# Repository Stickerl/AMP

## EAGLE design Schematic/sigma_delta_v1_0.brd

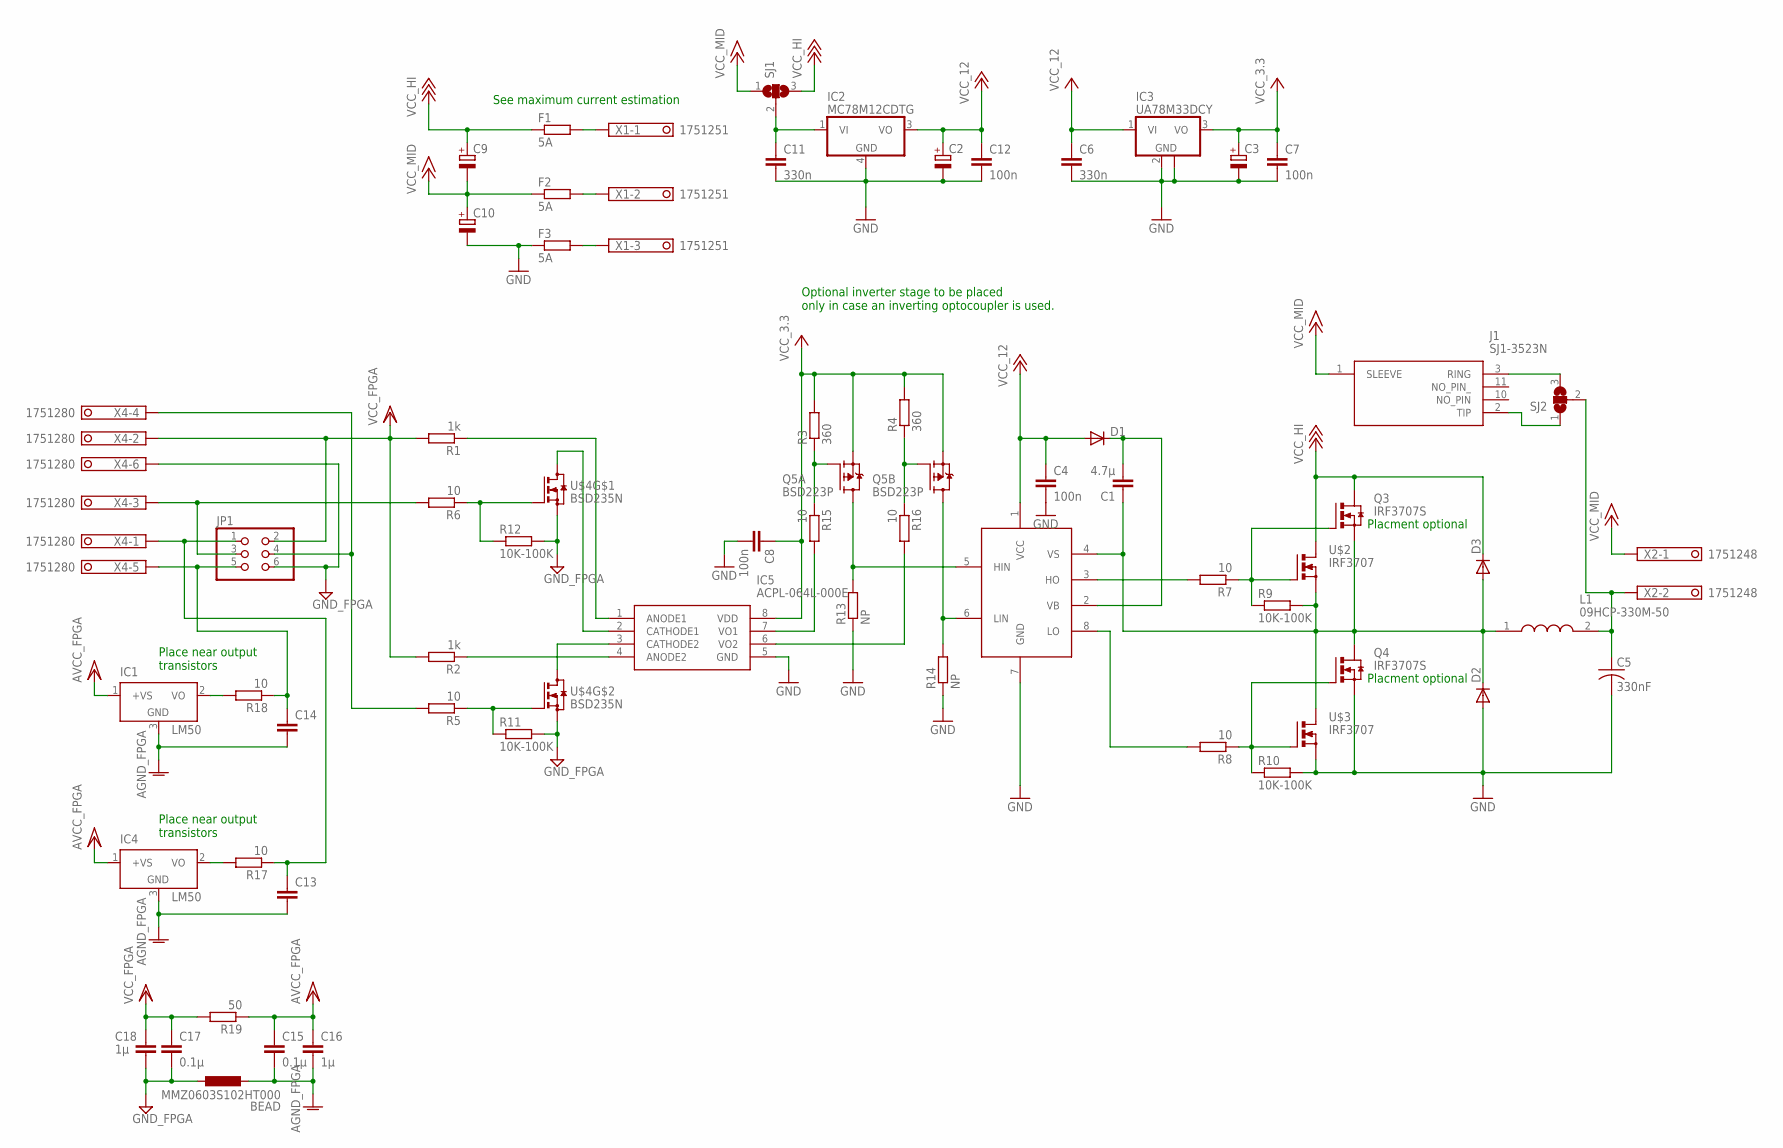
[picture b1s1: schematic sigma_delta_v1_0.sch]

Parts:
BEAD: MMZ0603S102HT000; L2012C
C1: 4.7µ; C0805K
C2, C3: CPOL-EUUD-6,3X7,7; UD-6,3X7,7_NICHICON
C4: 100n; C0805
C5: 330nF; C2220K
C6, C11: 330n; C0603
C7, C8, C12: 100n; C0603
C9, C10: CPOL-EUUD-10X10; UD-10X10_NICHICON
C13, C14: C-EUC0603; C0603
C15, C17: 0.1µ; C0603
C16, C18: 1µ; C0603
D1, D2, D3: DIODE-DO214AC; DO214AC
F1, F2, F3: 5A; M1206
IC1, IC4: LM50; SOT23
IC2: MC78M12CDTG; DPACK_3
IC3: UA78M33DCY; SOT223
IC5: ACPL-064L-000E; SOIC127P599X330-8N
J1: SJ1-3523N; SJ13523N
JP1: PINHD-2X3_2.54; 2X03
L1: 09HCP-330M-50; 09HCP330M50
Q3, Q4: IRF3707S; D2PACK
Q5: BSD223P; SOT363_INFINEON
R1, R2: 1k; R0603
R3, R4: 360; R0603
R5, R6, R7, R8, R15, R16, R17, R18: 10; R0603
R9, R10, R11, R12: 10K-100K; R0603
R13, R14: NP; R0603
R19: 50; R0603
SJ1: SJ2W; SJ_2
SJ2: SJ2WW; SJ_2W
U$1: IR2011; SO08
U$2, U$3: IRF3707; TO220BV
U$4: BSD235N; SOT65P210X100-6N
X1: 1751251
X2: 1751248
X4: 1751280

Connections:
AGND_FPGA: BEAD.2, C13.2, C14.2, C15.2, C16.2, IC1.3 (GND), IC4.3 (GND)
AVCC_FPGA: C15.1, C16.1, IC1.1 (+VS), IC4.1 (+VS), R19.1
GND: C2.-, C3.-, C4.2, C5.2, C6.2, C7.2, C8.2, C10.-, C11.2, C12.2, D2.A, F3.1, IC2.4 (GND), IC3.2 (GND), IC3.4 (GND), IC5.5 (GND), Q4.3 (S), R10.2, R13.1, R14.1, U$1.7 (GND), U$3.S
GND_FPGA: BEAD.1, C17.2, C18.2, JP1.6, R11.2, R12.2, U$4.1 (S), U$4.4 (S), X4.6
H_BRIDGE_MID: C1.1, D2.C, D3.A, L1.1, Q3.3 (S), Q4.2 (D), R9.2, U$1.4 (VS), U$2.S, U$3.D
unnamed: JP1.3, R6.2, X4.3
unnamed: JP1.4, R5.2, X4.4
unnamed: IC5.2 (CATHODE1), U$4.6 (D)
unnamed: IC5.3 (CATHODE2), U$4.3 (D)
unnamed: IC5.1 (ANODE1), R1.1
unnamed: IC5.4 (ANODE2), R2.1
unnamed: Q5.2 (G), R3.1, R15.1
unnamed: IC5.6 (VO2), R16.2
unnamed: F3.2, X1.3
unnamed: C5.1, L1.2, SJ2.2, X2.2
unnamed: R5.1, R11.1, U$4.5 (G)
unnamed: R6.1, R12.1, U$4.2 (G)
unnamed: R7.2, U$1.3 (HO)
unnamed: Q3.1 (G), R7.1, R9.1, U$2.G
unnamed: Q4.1 (G), R8.1, R10.1, U$3.G
unnamed: R8.2, U$1.8 (LO)
unnamed: C1.2, D1.C, U$1.2 (VB)
unnamed: F1.2, X1.1
unnamed: Q5.6 (D), R13.2, U$1.5 (HIN)
unnamed: F2.2, X1.2
unnamed: Q5.3 (D), R14.2, U$1.6 (LIN)
unnamed: Q5.5 (G), R4.1, R16.1
unnamed: IC4.2 (VO), R17.2
unnamed: J1.3 (RING), SJ2.3
unnamed: J1.2 (TIP), SJ2.1
unnamed: IC5.7 (VO1), R15.2
unnamed: C11.1, IC2.1 (VI), SJ1.2
unnamed: C13.1, JP1.1, R17.1, X4.1
unnamed: C14.1, JP1.5, R18.1, X4.5
unnamed: IC1.2 (VO), R18.2
VCC_3.3: C3.+, C7.1, C8.1, IC3.3 (VO), IC5.8 (VDD), Q5.1 (S), Q5.4 (S), R3.2, R4.2
VCC_12: C2.+, C4.1, C6.1, C12.1, D1.A, IC2.3 (VO), IC3.1 (VI), U$1.1 (VCC)
VCC_FPGA: C17.1, C18.1, JP1.2, R1.2, R2.2, R19.2, X4.2
VCC_HI: C9.+, D3.C, F1.1, Q3.2 (D), SJ1.3, U$2.D
VCC_MID: C9.-, C10.+, F2.1, J1.1 (SLEEVE), SJ1.1, X2.1

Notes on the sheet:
Placment optional
Place near output transistors
See maximum current estimation
Optional inverter stage to be placed only in case an inverting optocoupler is used.

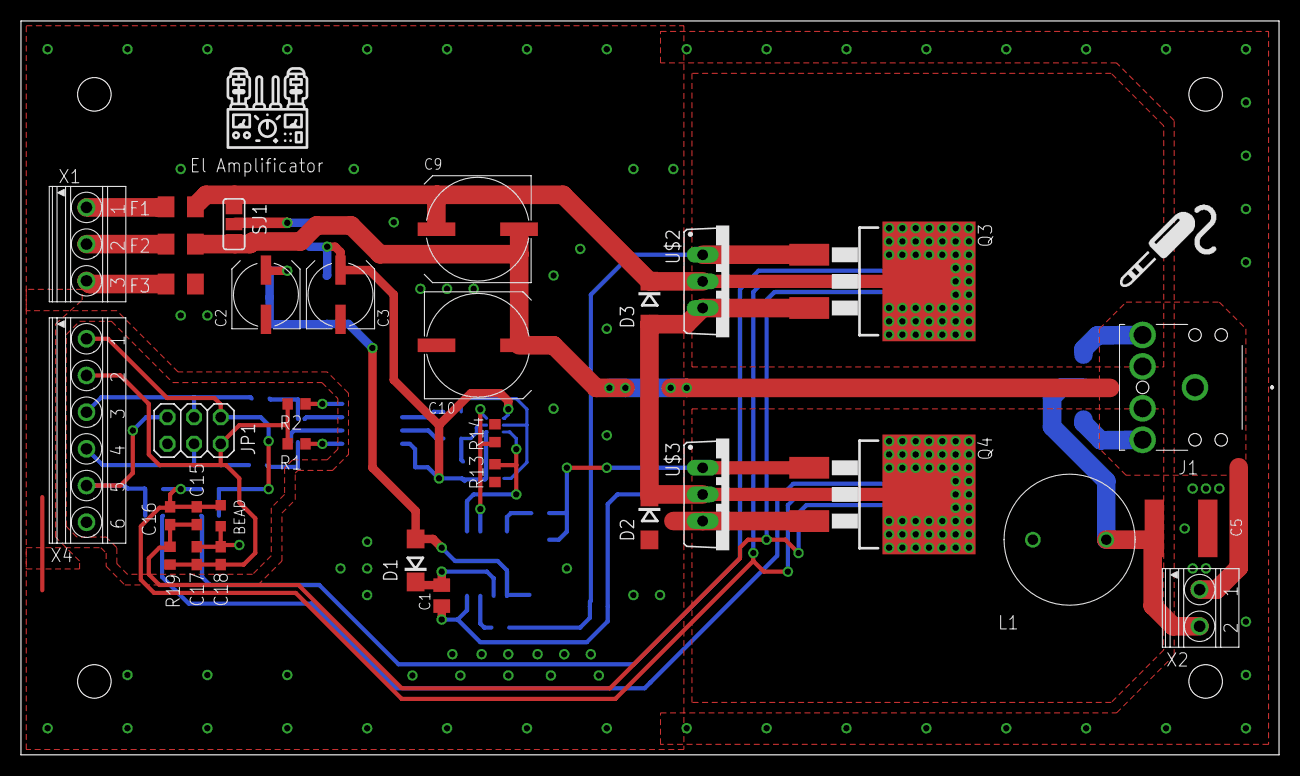
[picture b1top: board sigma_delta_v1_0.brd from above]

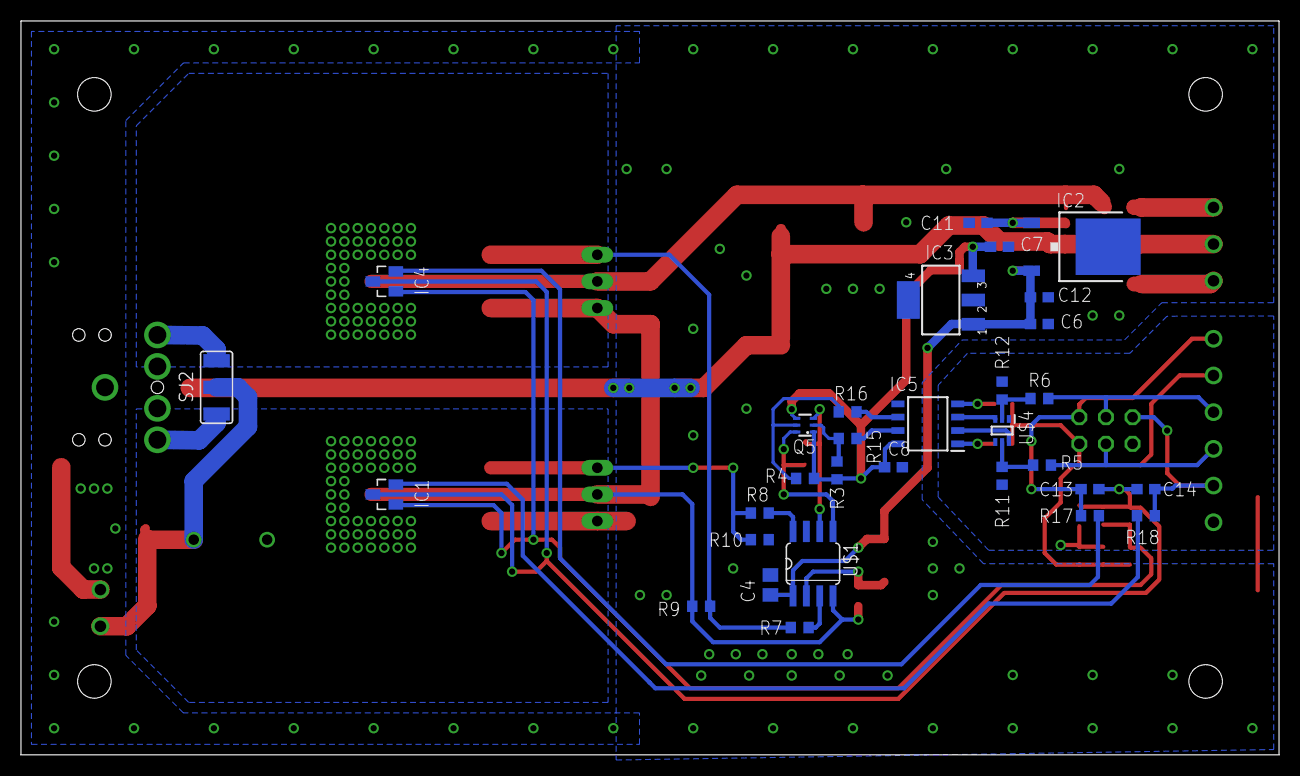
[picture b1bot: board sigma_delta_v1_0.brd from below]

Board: 2 copper layers, 120.0 x 70.0 mm, 64 parts (31 on the bottom side), 40 nets.

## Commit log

2020-01-31 copy contents from svn repo
2020-01-31 added script for sending audio data to the amp
2020-01-31 copied not committed svn files
2020-01-31 several bugfixes (project is not able to be compile)
2020-01-31 added files for AudioStreamFifo
2020-01-31 fixed a typo
2020-02-07 Added LabView project for simulation of the sigma delta structure.
2020-02-07 Added LabView project for debug bus and some additional vi's
2020-02-07 Moved Amplitude_compare.vi and Csv_read.vi into the debug bus project
2020-02-07 bug fixes in design, rework of UART_Tx_driver.vhd
2020-02-07 Added documents of DE0-Nano board.
2020-02-14 added pin assignment for UART pins commented all debugging outputs of sigmar delta modulator itself Received UART bytes are send out on debugging bus channel 0
2020-02-28 debugged tx driver (remainding buffer size seems to be transmitted correctly)
2020-03-13 replaced tabs with spaces
2020-03-13 bugfix: AudioFifo was in permanent reset reworked process for sending out debug data of audio stream before and after the FIFO upgraded AudioFifo version to version 18.1
2020-03-13 added experimental sending of several bytes in the HDLC protocol
2020-03-13 "made myRio application as startup application and changed View-Parallel-Port-Data.vi for debugging"
2020-03-13 added missing files of previous commit
2020-03-22 created a gitignore file
2020-03-22 added pins assignment of AMP project
2020-03-22 update git ignore file
2020-03-22 inverted bytes array sent to DUT
2020-03-22 added reset path to hdlc decoder
2020-03-22 added reading of CSV file to compare sent data with debug data
2020-03-22 added .csv generation to view-parallel-port-data vi and tested reading the file with python
2020-03-27 created a sub vi for csv file generation containing measuerment data
2020-03-27 forgot to save and close Labview before previous commit
2020-03-27 Implemented comparing a data stream sent to the FPGA and received back via csv-file
2020-03-27 Read in csv file and compare the data against an expectation -> verify communication stability
2020-03-28 set up testbench for validating transceived data via UART and debug bus
2020-04-03 reworked hdlc decoder. Bugfix: waiting for first frame delimiter. Endianess issue fixed (tested)
2020-04-10 removed LED and debug bus connection to the HDLC decoder output
2020-04-10 removed adc entity form top entity
2020-04-10 implemented sinus streaming in python. Somehow the buffersize response is worng
2020-04-17 added confirmation that this project is awesome!
2020-04-17 intermediate version of debugging uart data streaming.
2020-04-24 fixed first buffer fill level response and changed uart baudrate to 2mbit
2020-04-24 added debug bus connection to the HDLC decoder output again Revert "removed LED and debug bus connection to the HDLC decoder output"
    This reverts commit ebde65a294942e63edc34fb96ba66c52af91d544.
2020-04-24 commented out audiosample output on debugging bus
2020-04-30 fixed hdlc decoding issue. Audiostreaming currently works with a sine amplitude of 1000 only. Underflow exception occures within the python script
2020-05-08 fixed bugs in Uart transmission and successfully verified bitstream (filtered) vs simulation output
2020-05-08 added eagle schematic
2020-05-22 unsuccessfully tried to stream a audio file
2020-07-10 first successfull stream of an audio file to the FPGA
2020-07-10 added connection between VS and the Load within the scematic
2020-08-07 started reworking the scematic
2020-08-30 Added documents and eagle librarys as well as Part_List.xlsx
2020-08-30 Add data sheet for audio jack
2020-08-30 added datasheetd and pinheader library
2020-08-30 intermediate commit before rework of the input stage
2020-08-30 Added datasheet for dual channel N MOS BSD223P. Added several parts to the Part_list
2020-08-30 Added NMOS pair for data transfer
2020-09-25 adde datasheet of BSD235N
2020-09-25 continued replaceing parts with smd components
2020-10-02 Add data sheet for optocoupler.
2020-10-02 Add optocoupler to part list
2020-10-02 finished rework of the Schematic and cleaned up repository
2020-10-02 started layout design
2020-10-09 continued layouting and added analog decoupling for temperature sensors
2020-10-16 continued routing and added ferrit bead datasheet
2020-10-23 added FPGA_GND polygon to the top layer
2020-10-23 intermediate commit prior changing the net to mm
2020-10-23 Finished layouting. DRC pending
2020-11-01 adapted wireing width of power stage and exchanged bootstrap capacitor
2020-11-06 ERC and DRC done. Ready for production.
2020-11-06 added mounting drills
2020-11-06 generated gerber files for manufacturing
2020-11-13 add mouser link to fuse
2020-11-13 add 3.3V regulator to part list
2020-11-13 added parts to part list
2020-11-13 dummy change to check connectivity to repository
2020-11-13 revert last change
2020-11-22 Removed datasheet of deprecated optocouppler
2020-11-22 added non inverting optocoupler as suppliment of ACPL-064L
2020-11-22 added comment to the scematic regarding the inverter stage
2020-11-27 Add Maxima trial file
2020-12-04 started transferring math work from maple to maxima
2020-12-18 reworked gerber files
2021-01-01 add block diagram of first order sigma delta
2021-01-01 added transfer functions for E and X
2021-01-01 corrected an error in noise transfer function
2021-01-02 added maple files and added calculations fo first order sigma delta modulator
2021-01-08 debugged of 3d plot of transfer function
2021-01-08 Banana commit to verify, that i can still access the repository while the git config was changed
2021-10-29 It is now possible to generate a 3d plot of the abs() of He(z)
2021-11-05 Introduce headings and table of contents for noise transfer function
2021-11-05 beautify Bode Diagram plot
2021-11-05 started to evalute signal transfer function
2024-05-31 Add draft of 1st order sigma delta
2024-05-31 Add 3rd order sigma delta calculation inspired by ChatGPT
2024-06-07 Add some literature and block diagrams
2024-07-26 add block diagram for 1st order sigma delta - this time right
2024-07-26 add sigma delta 1st order dimensioning
